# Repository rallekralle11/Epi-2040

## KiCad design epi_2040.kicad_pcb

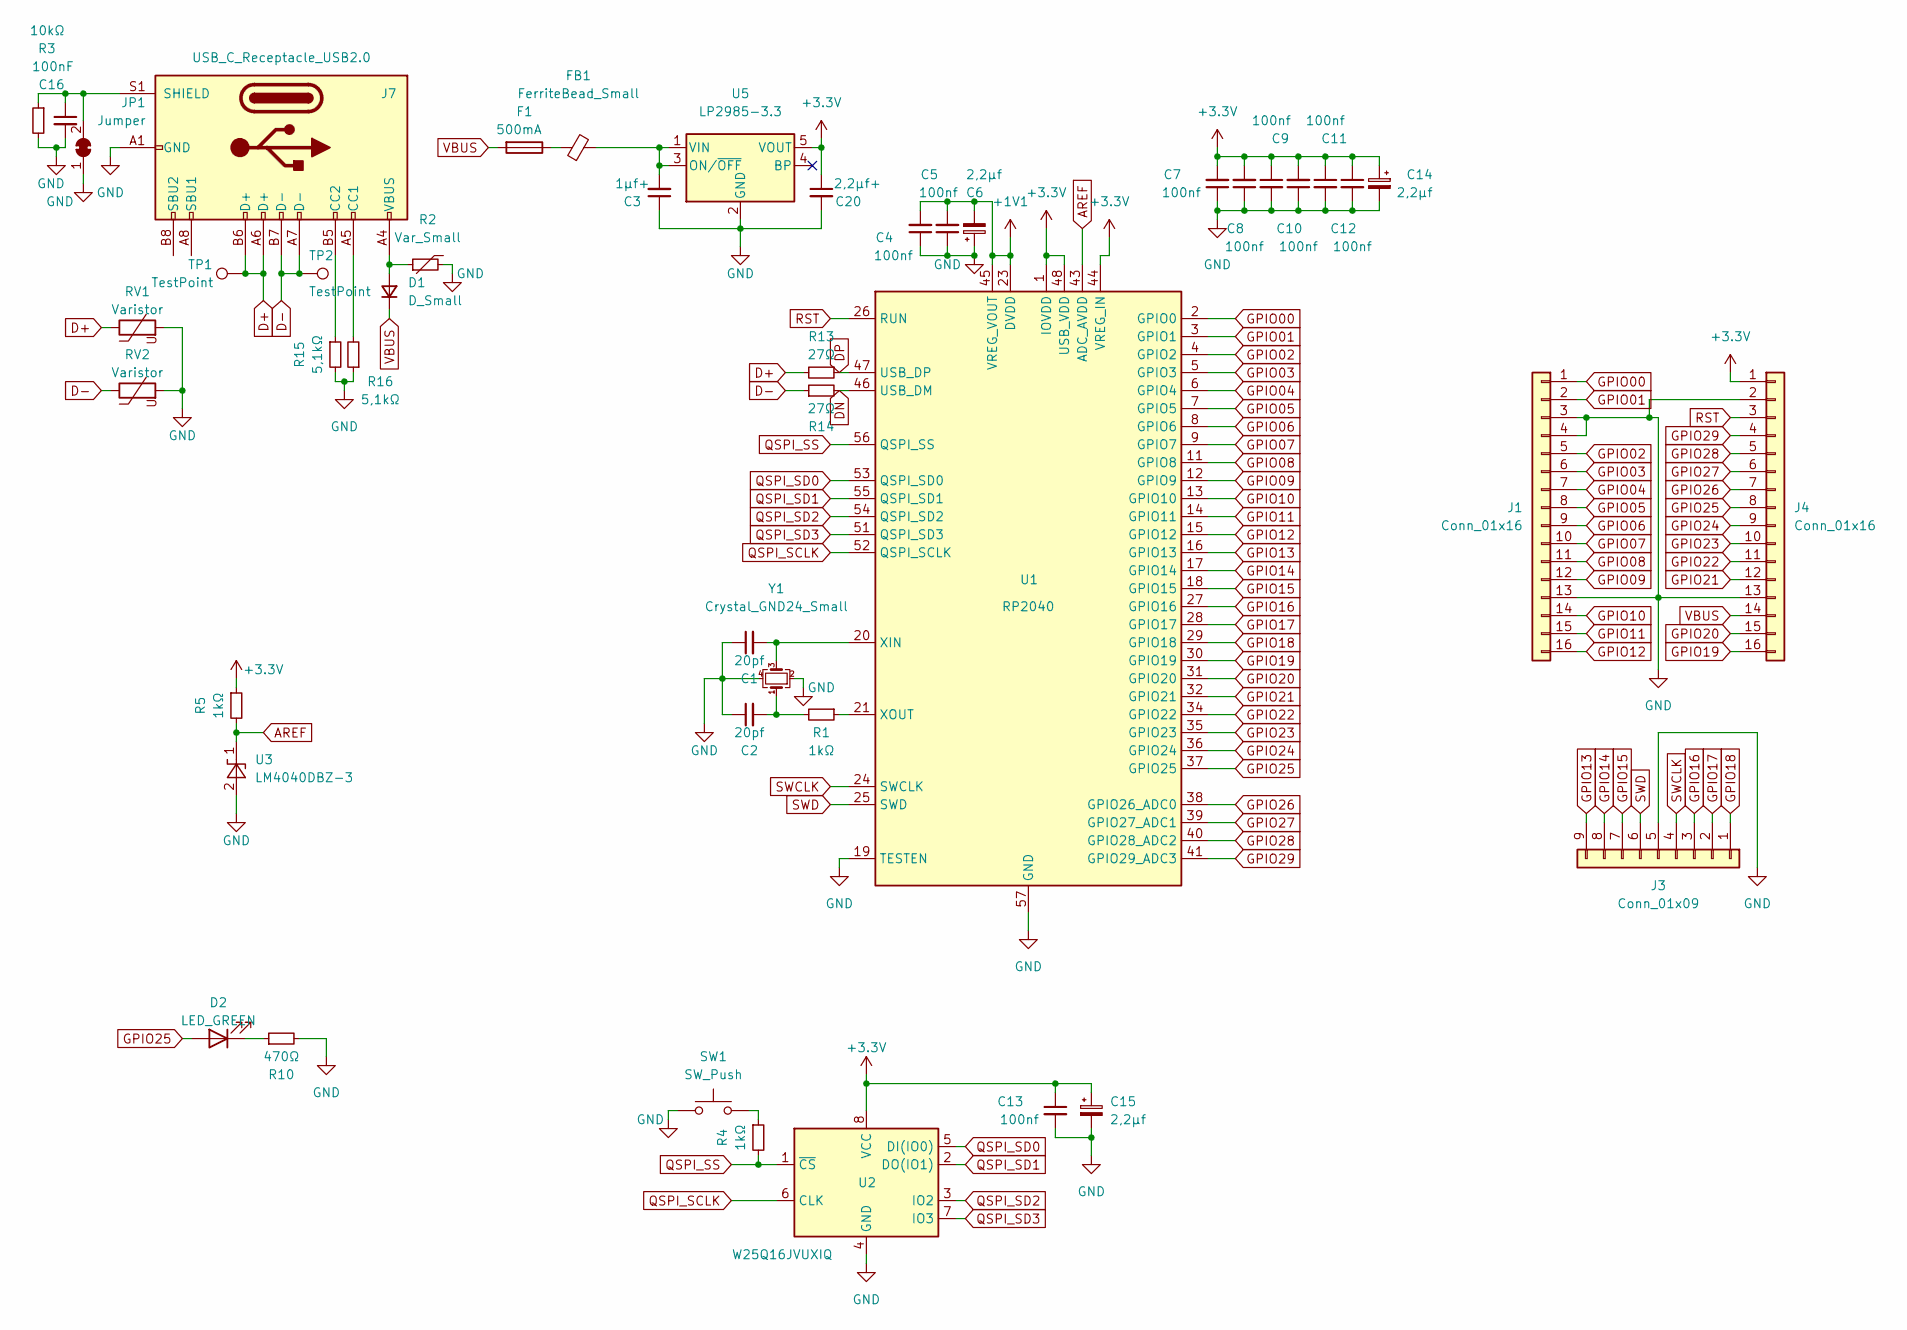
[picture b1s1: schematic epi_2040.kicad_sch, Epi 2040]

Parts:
C1, C2: 20pf; C_0402_1005Metric
C3: 1µf+; C_0402_1005Metric
C4, C5, C7, C8, C9, C10, C11, C12, C13: 100nf; C_0402_1005Metric
C6, C14, C15: 2,2µf; C_0402_1005Metric
C16: 100nF; R_0402_1005Metric
C20: 2,2µf+; C_0402_1005Metric
D1: D_Small; D_SOD-323
D2: LED_GREEN; LED_0402_1005Metric
F1: 500mA; Fuse_0402_1005Metric
FB1: FerriteBead_Small; R_0402_1005Metric
J1, J4: Conn_01x16; PinHeader_1x16_P1.27mm_Vertical
J3: Conn_01x09; PinHeader_1x09_P1.27mm_Vertical
J7: USB_C_Receptacle_USB2.0; USB-C MC-314C-4P16_V2 (2023_01_13 17_48_46 UTC)
JP1: Jumper; SolderJumper-2_P1.3mm_Bridged_RoundedPad1.0x1.5mm
R1, R4, R5: 1kΩ; R_0402_1005Metric
R2: Var_Small; R_0402_1005Metric
R3: 10kΩ; R_0402_1005Metric
R10: 470Ω; R_0402_1005Metric
R13, R14: 27Ω; R_0402_1005Metric
R15, R16: 5,1kΩ; R_0402_1005Metric
RV1, RV2: Varistor; R_0402_1005Metric
SW1: SW_Push; R-668048
TP1, TP2: TestPoint; TestPoint_Pad_1.0x1.0mm
U1: RP2040; QFN-56-1EP_7x7mm_P0.4mm_EP3.2x3.2mm
U2: W25Q16JVUXIQ; SON-8-1EP_3x2mm_P0.5mm_EP1.4x1.6mm
U3: LM4040DBZ-3; SOT-23_bättre (2022_12_20 17_46_41 UTC)
U5: LP2985-3.3; SOT-23-5
Y1: Crystal_GND24_Small; Crystal_SMD_2520-4Pin_2.5x2.0mm

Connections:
+1V1: C4.2, C5.2, C6.2, U1.23 (DVDD), U1.45 (VREG_VOUT), U1.50 (DVDD)
+3.3V: C7.2, C8.2, C9.1, C10.2, C11.1, C12.1, C13.1, C14.1, C15.1, C20.1, J4.1, R5.1, U1.1 (IOVDD), U1.10 (IOVDD), U1.22 (IOVDD), U1.33 (IOVDD), U1.42 (IOVDD), U1.44 (VREG_IN), U1.48 (USB_VDD), U1.49 (IOVDD), U2.8 (VCC), U5.5 (VOUT)
AREF: R5.2, U1.43 (ADC_AVDD), U3.1 (K)
D+: J7.A6 (D+), J7.B6 (D+), R13.2, RV1.1, TP1.1
D-: J7.A7 (D-), J7.B7 (D-), R14.1, RV2.1, TP2.1
DN: R14.2, U1.46 (USB_DM)
DP: R13.1, U1.47 (USB_DP)
GND: C1.1, C2.1, C3.1, C4.1, C5.1, C6.1, C7.1, C8.1, C9.2, C10.1, C11.2, C12.2, C13.2, C14.2, C15.2, C16.2, C20.2, J1.3, J1.4, J1.13, J3.5, J4.2, J4.13, J7.A1 (GND), J7.A12 (GND), J7.B1 (GND), J7.B12 (GND), JP1.1 (A), R2.2, R3.2, R10.2, R15.2, R16.1, RV1.2, RV2.2, SW1.1, U1.19 (TESTEN), U1.57 (GND), U2.4 (GND), U3.2 (A), U5.2 (GND), Y1.2, Y1.4
GPIO00: J1.1, U1.2 (GPIO0)
GPIO01: J1.2, U1.3 (GPIO1)
GPIO02: J1.5, U1.4 (GPIO2)
GPIO03: J1.6, U1.5 (GPIO3)
GPIO04: J1.7, U1.6 (GPIO4)
GPIO05: J1.8, U1.7 (GPIO5)
GPIO06: J1.9, U1.8 (GPIO6)
GPIO07: J1.10, U1.9 (GPIO7)
GPIO08: J1.11, U1.11 (GPIO8)
GPIO09: J1.12, U1.12 (GPIO9)
GPIO10: J1.14, U1.13 (GPIO10)
GPIO11: J1.15, U1.14 (GPIO11)
GPIO12: J1.16, U1.15 (GPIO12)
GPIO13: J3.9, U1.16 (GPIO13)
GPIO14: J3.8, U1.17 (GPIO14)
GPIO15: J3.7, U1.18 (GPIO15)
GPIO16: J3.3, U1.27 (GPIO16)
GPIO17: J3.2, U1.28 (GPIO17)
GPIO18: J3.1, U1.29 (GPIO18)
GPIO19: J4.16, U1.30 (GPIO19)
GPIO20: J4.15, U1.31 (GPIO20)
GPIO21: J4.12, U1.32 (GPIO21)
GPIO22: J4.11, U1.34 (GPIO22)
GPIO23: J4.10, U1.35 (GPIO23)
GPIO24: J4.9, U1.36 (GPIO24)
GPIO25: D2.2 (A), J4.8, U1.37 (GPIO25)
GPIO26: J4.7, U1.38 (GPIO26_ADC0)
GPIO27: J4.6, U1.39 (GPIO27_ADC1)
GPIO28: J4.5, U1.40 (GPIO28_ADC2)
GPIO29: J4.4, U1.41 (GPIO29_ADC3)
unnamed: C2.2, R1.2, Y1.1
unnamed: D1.2 (A), J7.A4 (VBUS), J7.A9 (VBUS), J7.B4 (VBUS), J7.B9 (VBUS), R2.1
unnamed: D2.1 (K), R10.1
unnamed: F1.1, FB1.1
unnamed: J7.A5 (CC1), R16.2
unnamed: J7.B5 (CC2), R15.1
unnamed: C16.1, J7.S1 (SHIELD), JP1.2 (B), R3.1
unnamed: R4.1, SW1.3
unnamed: C1.2, U1.20 (XIN), Y1.3
unnamed: R1.1, U1.21 (XOUT)
unnamed: C3.2, FB1.2, U5.1 (VIN), U5.3 (ON/~OFF)
QSPI_SCLK: U1.52 (QSPI_SCLK), U2.6 (CLK)
QSPI_SD0: U1.53 (QSPI_SD0), U2.5 (DI(IO0))
QSPI_SD1: U1.55 (QSPI_SD1), U2.2 (DO(IO1))
QSPI_SD2: U1.54 (QSPI_SD2), U2.3 (IO2)
QSPI_SD3: U1.51 (QSPI_SD3), U2.7 (IO3)
QSPI_SS: R4.2, U1.56 (QSPI_SS), U2.1 (~CS)
RST: J4.3, U1.26 (RUN)
SWCLK: J3.4, U1.24 (SWCLK)
SWD: J3.6, U1.25 (SWD)
VBUS: D1.1 (K), F1.2, J4.14

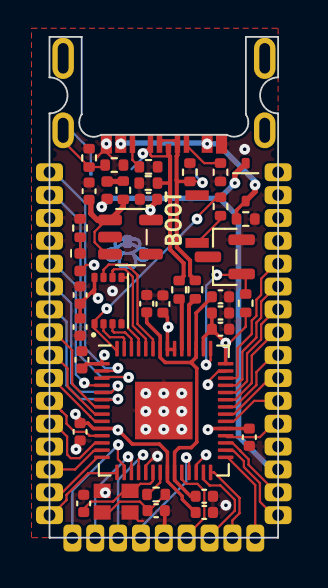
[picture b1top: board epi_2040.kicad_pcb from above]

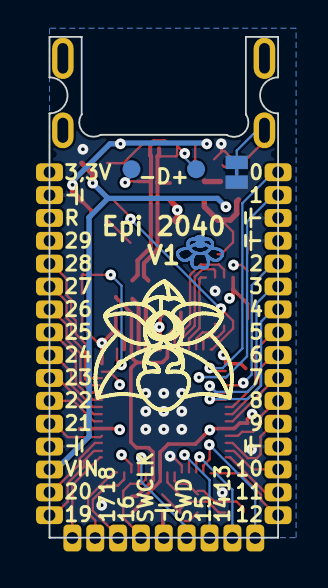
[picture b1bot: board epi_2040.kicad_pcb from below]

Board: 4 copper layers, 12.7 x 27.8 mm, 46 parts (3 on the bottom side), 59 nets.

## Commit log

2024-02-04 init
2024-02-04 pictures
